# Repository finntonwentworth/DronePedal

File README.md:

# Drone Pedal/ Synth 

Repository for Drone pedal I have been working on and designing 

LFO Design from Skull and Circuits

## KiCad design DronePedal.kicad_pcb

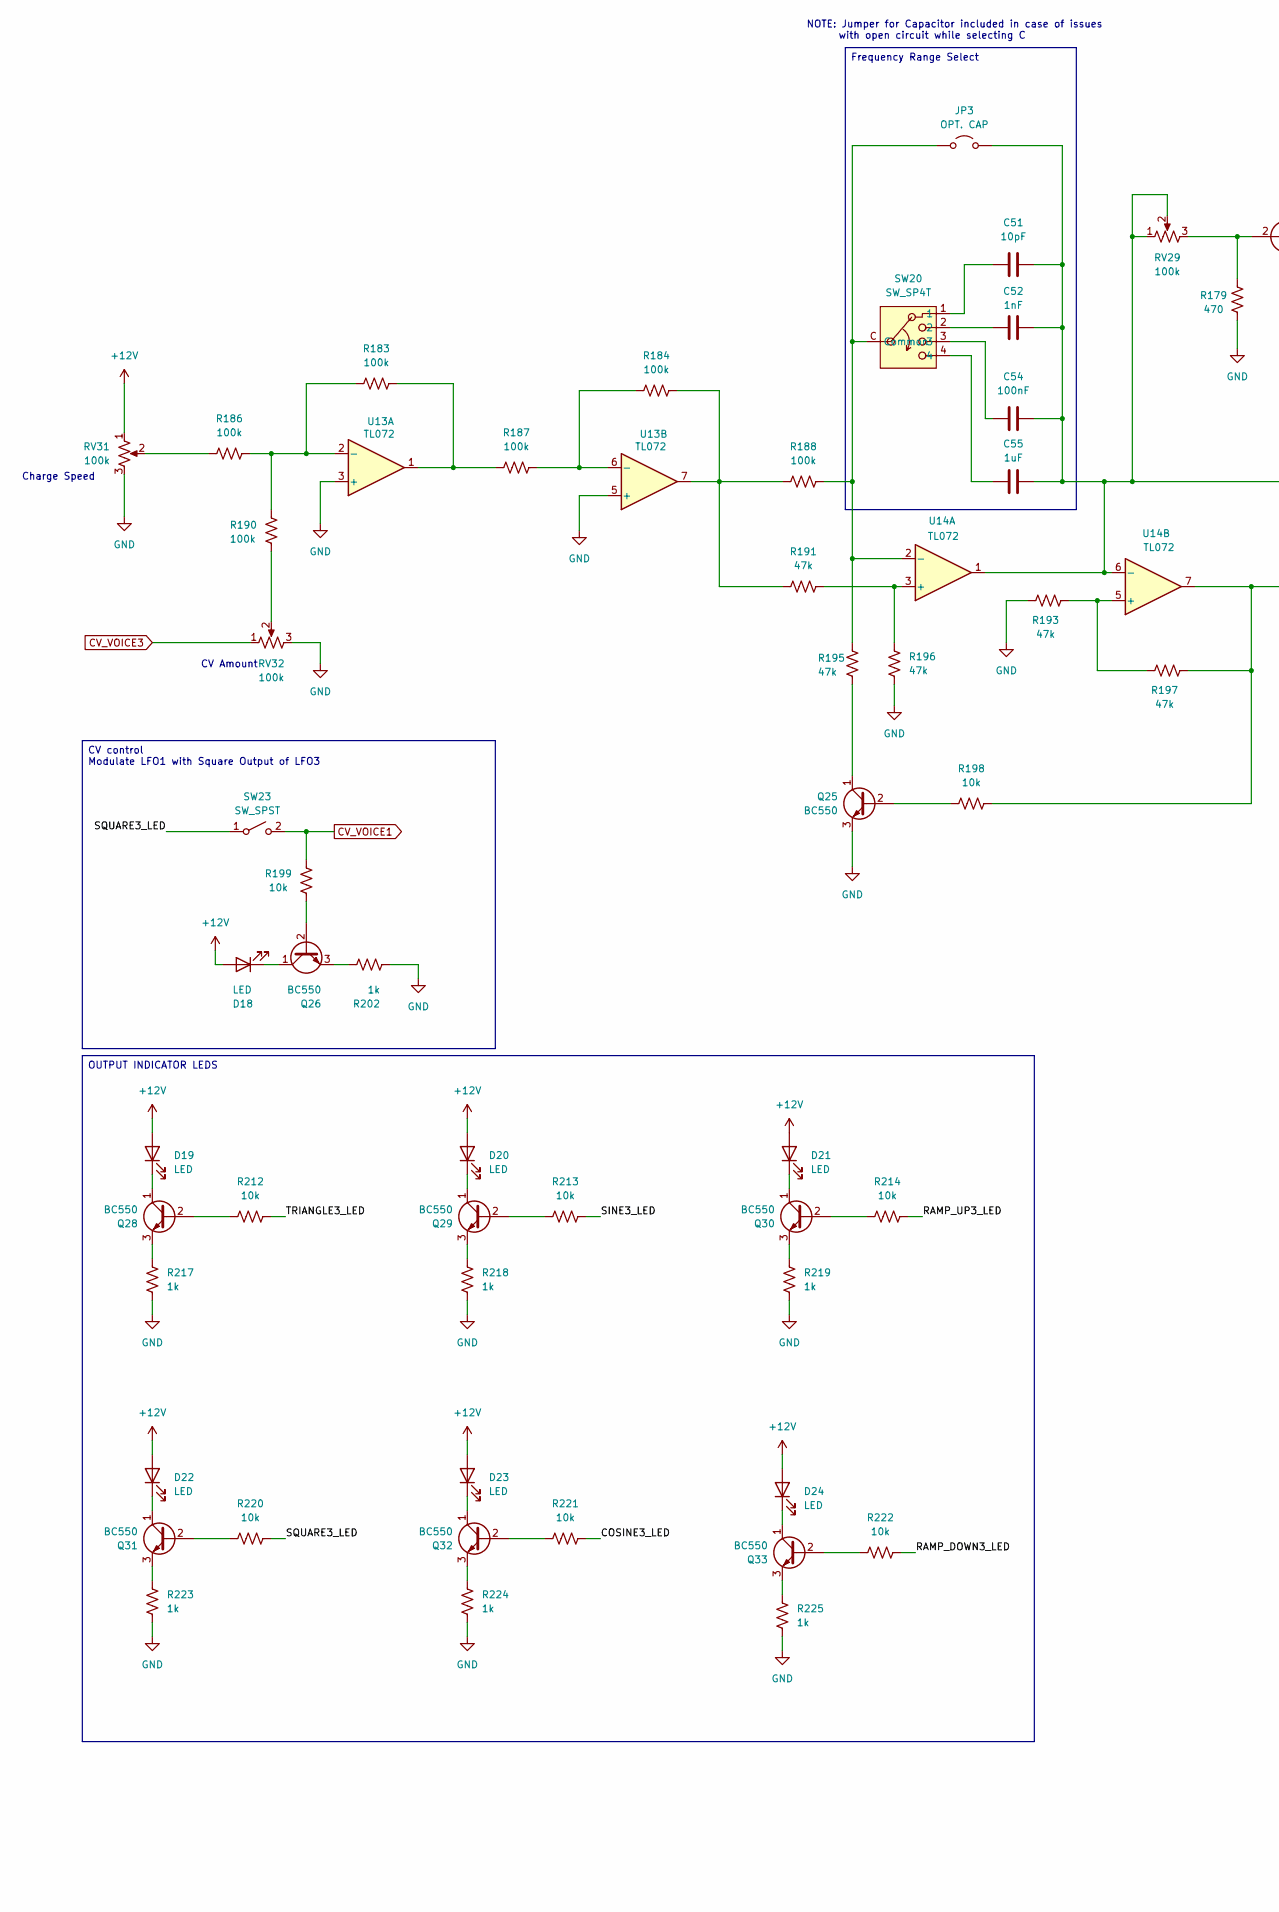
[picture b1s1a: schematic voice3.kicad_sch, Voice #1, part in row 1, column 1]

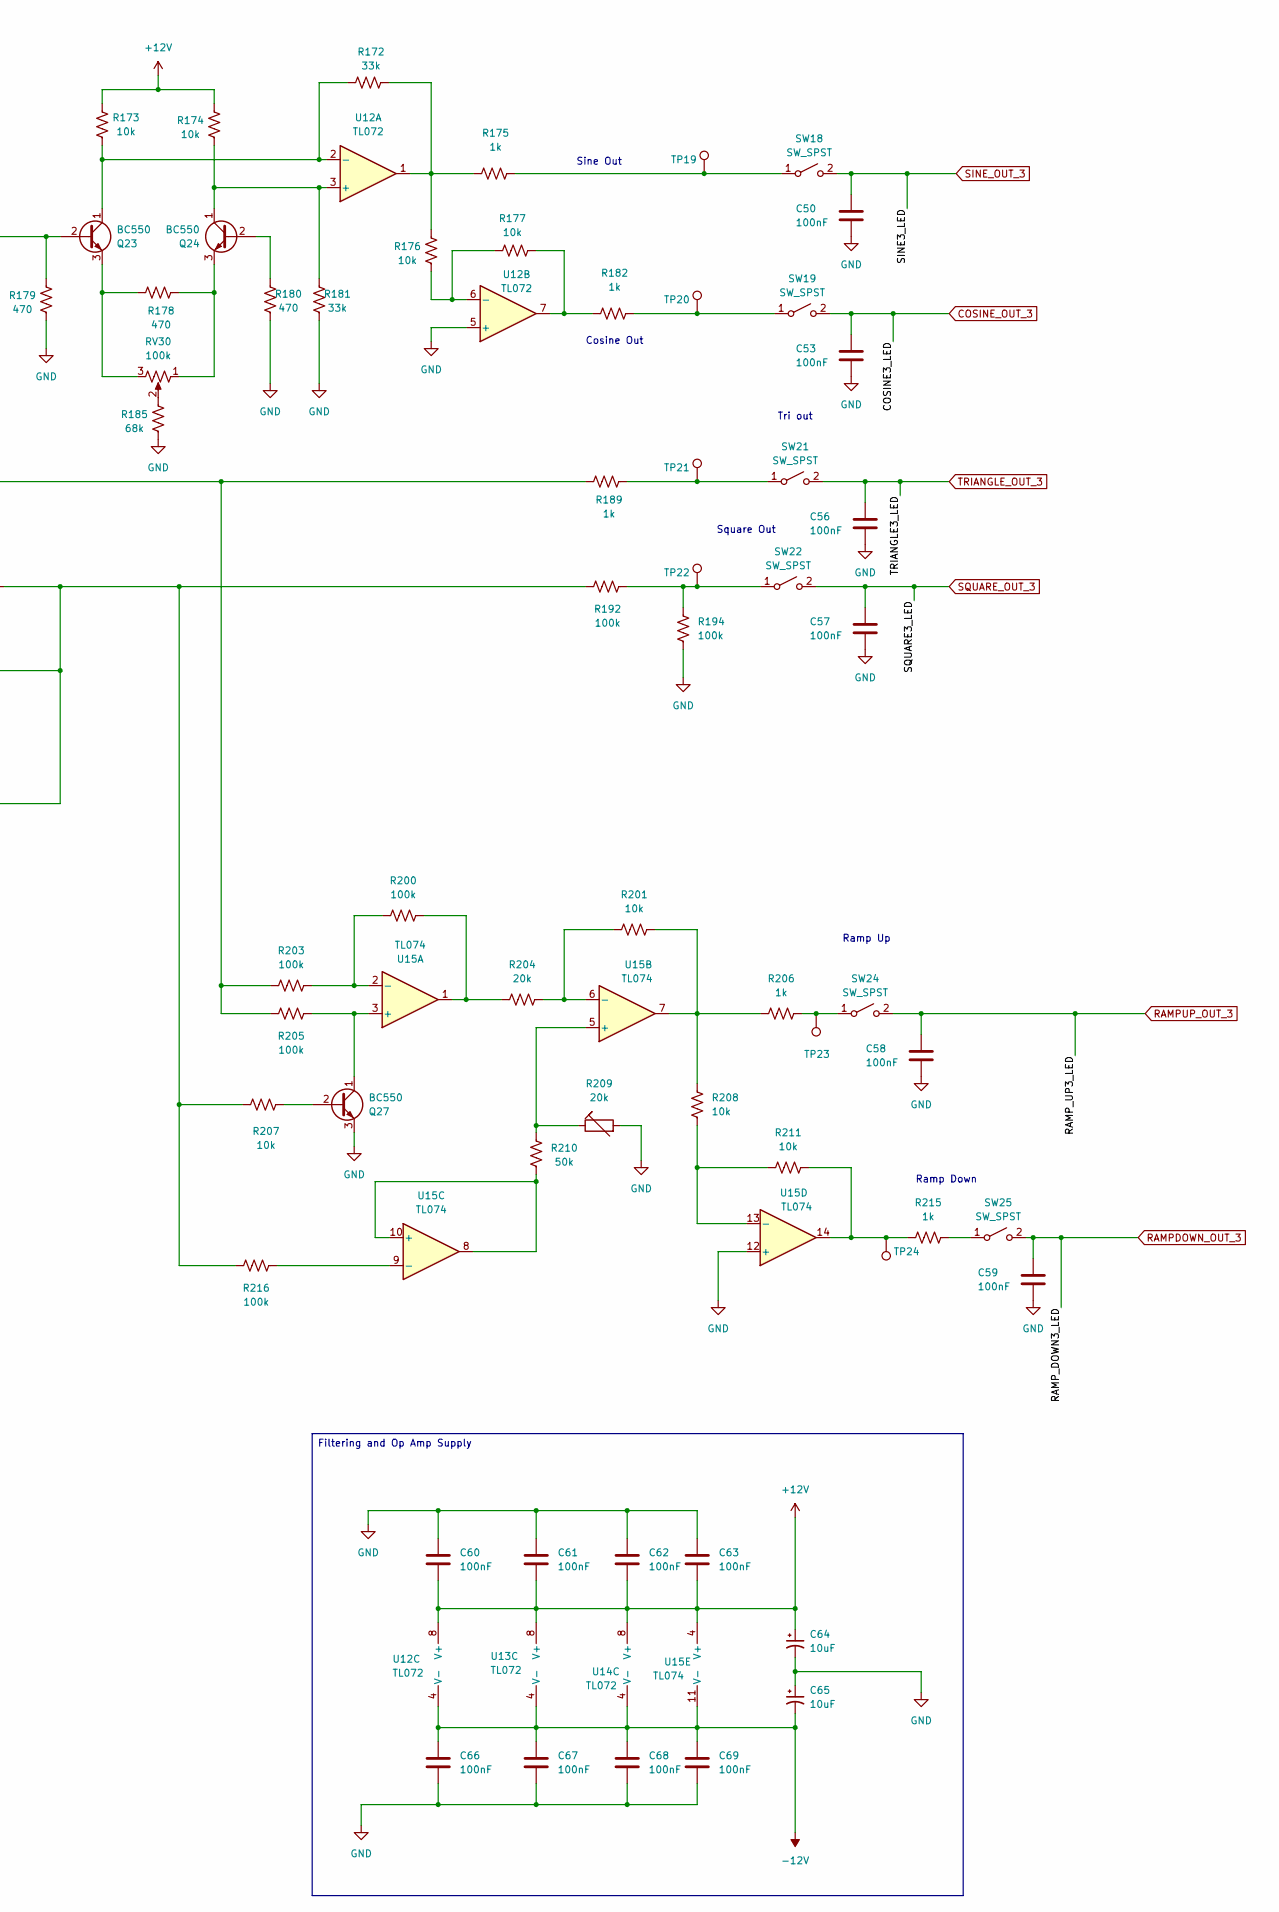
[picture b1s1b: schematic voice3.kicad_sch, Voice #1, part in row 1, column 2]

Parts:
C50, C53, C54, C56, C57, C58, C59, C60, C61, C62, C63, C66, C67, C68, C69: 100nF; C_Disc_D6.0mm_W2.5mm_P5.00mm
C51: 10pF; C_Disc_D4.7mm_W2.5mm_P5.00mm
C52: 1nF; C_Disc_D6.0mm_W2.5mm_P5.00mm
C55: 1uF; C_Disc_D5.0mm_W2.5mm_P2.50mm
C64, C65: 10uF; C_Disc_D6.0mm_W2.5mm_P5.00mm
D18, D19, D20, D21, D22, D23, D24: LED; LED_D1.8mm_W3.3mm_H2.4mm
JP3: OPT. CAP; C_Disc_D5.0mm_W2.5mm_P2.50mm
Q23, Q24, Q25, Q26, Q27, Q28, Q29, Q30, Q31, Q32, Q33: BC550; TO-92_Inline
R172, R181: 33k; R_Axial_DIN0204_L3.6mm_D1.6mm_P5.08mm_Horizontal
R173, R174, R176, R177, R198, R199, R201, R207, R208, R211, R212, R213, R214, R220, R221, R222: 10k; R_Axial_DIN0204_L3.6mm_D1.6mm_P5.08mm_Horizontal
R175, R182, R189, R202, R206, R215, R217, R218, R219, R223, R224, R225: 1k; R_Axial_DIN0204_L3.6mm_D1.6mm_P5.08mm_Horizontal
R178, R179, R180: 470; R_Axial_DIN0204_L3.6mm_D1.6mm_P5.08mm_Horizontal
R183, R184, R186, R187, R188, R190, R192, R194, R200, R203, R205, R216: 100k; R_Axial_DIN0207_L6.3mm_D2.5mm_P10.16mm_Horizontal
R185: 68k; R_Axial_DIN0204_L3.6mm_D1.6mm_P5.08mm_Horizontal
R191, R193, R195, R196, R197: 47k; R_Axial_DIN0204_L3.6mm_D1.6mm_P5.08mm_Horizontal
R204: 20k; R_Axial_DIN0204_L3.6mm_D1.6mm_P5.08mm_Horizontal
R209: 20k; PinHeader_1x03_P2.54mm_Vertical
R210: 50k; R_Axial_DIN0207_L6.3mm_D2.5mm_P7.62mm_Horizontal
RV29, RV30, RV31, RV32: 100k; PinHeader_1x03_P2.54mm_Vertical
SW18, SW19, SW21, SW22, SW23, SW24, SW25: SW_SPST; PinHeader_1x02_P2.54mm_Vertical
SW20: SW_SP4T; PinHeader_1x05_P2.54mm_Vertical
TP19, TP20, TP21, TP22, TP23, TP24: TestPoint_Pad_D1.0mm
U12, U13, U14: TL072; DIP-8_W7.62mm
U15: TL074; DIP-14_W7.62mm

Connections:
+12V: C60.2, C61.2, C62.2, C63.2, C64.1, D18.2 (A), D19.2 (A), D20.2 (A), D21.2 (A), D22.2 (A), D23.2 (A), D24.2 (A), R173.1, R174.1, RV31.1, U12.8 (V+), U13.8 (V+), U14.8 (V+), U15.4 (V+); also elsewhere on the board
-12V: C65.2, C66.1, C67.1, C68.1, C69.1, U12.4 (V-), U13.4 (V-), U14.4 (V-), U15.11 (V-); also elsewhere on the board
COSINE_OUT_3: C53.1, R221.2, SW19.2 (B); also elsewhere on the board
CV_VOICE1: R199.2, SW23.2 (B); also elsewhere on the board
CV_VOICE3: RV32.1; also elsewhere on the board
GND: C50.2, C53.2, C56.2, C57.2, C58.2, C59.2, C60.1, C61.1, C62.1, C63.1, C64.2, C65.1, C66.2, C67.2, C68.2, C69.2, Q25.3 (E), Q27.3 (E), R179.2, R180.1, R181.1, R185.2, R193.2, R194.1, R196.1, R202.1, R209.2, R217.1, R218.1, R219.1, R223.1, R224.1, R225.1, RV31.3, RV32.3, U12.5 (+), U13.3 (+), U13.5 (+), U15.12 (+); also elsewhere on the board
unnamed: C51.1, SW20.1
unnamed: C52.2, SW20.2
unnamed: C54.2, SW20.3
unnamed: C55.2, SW20.4
unnamed: D18.1 (K), Q26.1 (C)
unnamed: D19.1 (K), Q28.1 (C)
unnamed: D20.1 (K), Q29.1 (C)
unnamed: D21.1 (K), Q30.1 (C)
unnamed: D22.1 (K), Q31.1 (C)
unnamed: D23.1 (K), Q32.1 (C)
unnamed: D24.1 (K), Q33.1 (C)
unnamed: JP3.1 (A), R188.2, R195.2, SW20.C (Common), U14.2 (-)
unnamed: C51.2, C52.1, C54.1, C55.1, JP3.2 (B), R189.2, R203.1, R205.1, RV29.1, RV29.2, U14.1, U14.6 (-)
unnamed: Q23.2 (B), R179.1, RV29.3
unnamed: Q23.1 (C), R172.2, R173.2, U12.2 (-)
unnamed: Q23.3 (E), R178.1, RV30.3
unnamed: Q24.2 (B), R180.2
unnamed: Q24.1 (C), R174.2, R181.2, U12.3 (+)
unnamed: Q24.3 (E), R178.2, RV30.1
unnamed: Q25.2 (B), R198.1
unnamed: Q25.1 (C), R195.1
unnamed: Q26.2 (B), R199.1
unnamed: Q26.3 (E), R202.2
unnamed: Q27.2 (B), R207.2
unnamed: Q27.1 (C), R205.2, U15.3 (+)
unnamed: Q28.2 (B), R212.1
unnamed: Q28.3 (E), R217.2
unnamed: Q29.2 (B), R213.1
unnamed: Q29.3 (E), R218.2
unnamed: Q30.2 (B), R214.1
unnamed: Q30.3 (E), R219.2
unnamed: Q31.2 (B), R220.1
unnamed: Q31.3 (E), R223.2
unnamed: Q32.2 (B), R221.1
unnamed: Q32.3 (E), R224.2
unnamed: Q33.2 (B), R222.1
unnamed: Q33.3 (E), R225.2
unnamed: R172.1, R175.2, R176.1, U12.1
unnamed: R177.1, R182.2, U12.7
unnamed: R183.2, R187.1, U13.1
unnamed: R184.2, R188.1, R191.1, U13.7
unnamed: R185.1, RV30.2
unnamed: R186.1, RV31.2
unnamed: R190.1, RV32.2
unnamed: R192.1, R197.1, R198.2, R207.1, R216.1, U14.7
unnamed: R200.2, R204.1, U15.1
unnamed: R201.2, R206.1, R208.2, U15.7
unnamed: R211.1, R215.2, TP24.1, U15.14
unnamed: R175.1, SW18.1 (A), TP19.1
unnamed: R182.1, SW19.1 (A), TP20.1
unnamed: R189.1, SW21.1 (A), TP21.1
unnamed: R192.2, R194.2, SW22.1 (A), TP22.1
unnamed: R206.2, SW24.1 (A), TP23.1
unnamed: R215.1, SW25.1 (A)
unnamed: R176.2, R177.2, U12.6 (-)
unnamed: R183.1, R186.2, R190.2, U13.2 (-)
unnamed: R184.1, R187.2, U13.6 (-)
unnamed: R191.2, R196.2, U14.3 (+)
unnamed: R193.1, R197.2, U14.5 (+)
unnamed: R200.1, R203.2, U15.2 (-)
unnamed: R209.1, R210.2, U15.5 (+)
unnamed: R201.1, R204.2, U15.6 (-)
unnamed: R210.1, U15.8, U15.10 (+)
unnamed: R216.2, U15.9 (-)
unnamed: R208.1, R211.2, U15.13 (-)
RAMPDOWN_OUT_3: C59.1, R222.2, SW25.2 (B); also elsewhere on the board
RAMPUP_OUT_3: C58.1, R214.2, SW24.2 (B); also elsewhere on the board
SINE_OUT_3: C50.1, R213.2, SW18.2 (B); also elsewhere on the board
SQUARE_OUT_3: C57.1, R220.2, SW22.2 (B), SW23.1 (A); also elsewhere on the board
TRIANGLE_OUT_3: C56.1, R212.2, SW21.2 (B); also elsewhere on the board

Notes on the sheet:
NOTE: Jumper for Capacitor included in case of issues with open circuit while selecting C
Charge Speed
CV Amount
Square Out
Sine Out
Tri out
Cosine Out
Ramp Up
Ramp Down
Frequency Range Select
CV control Modulate LFO1 with Square Output of LFO3
OUTPUT INDICATOR LEDS
Filtering and Op Amp Supply

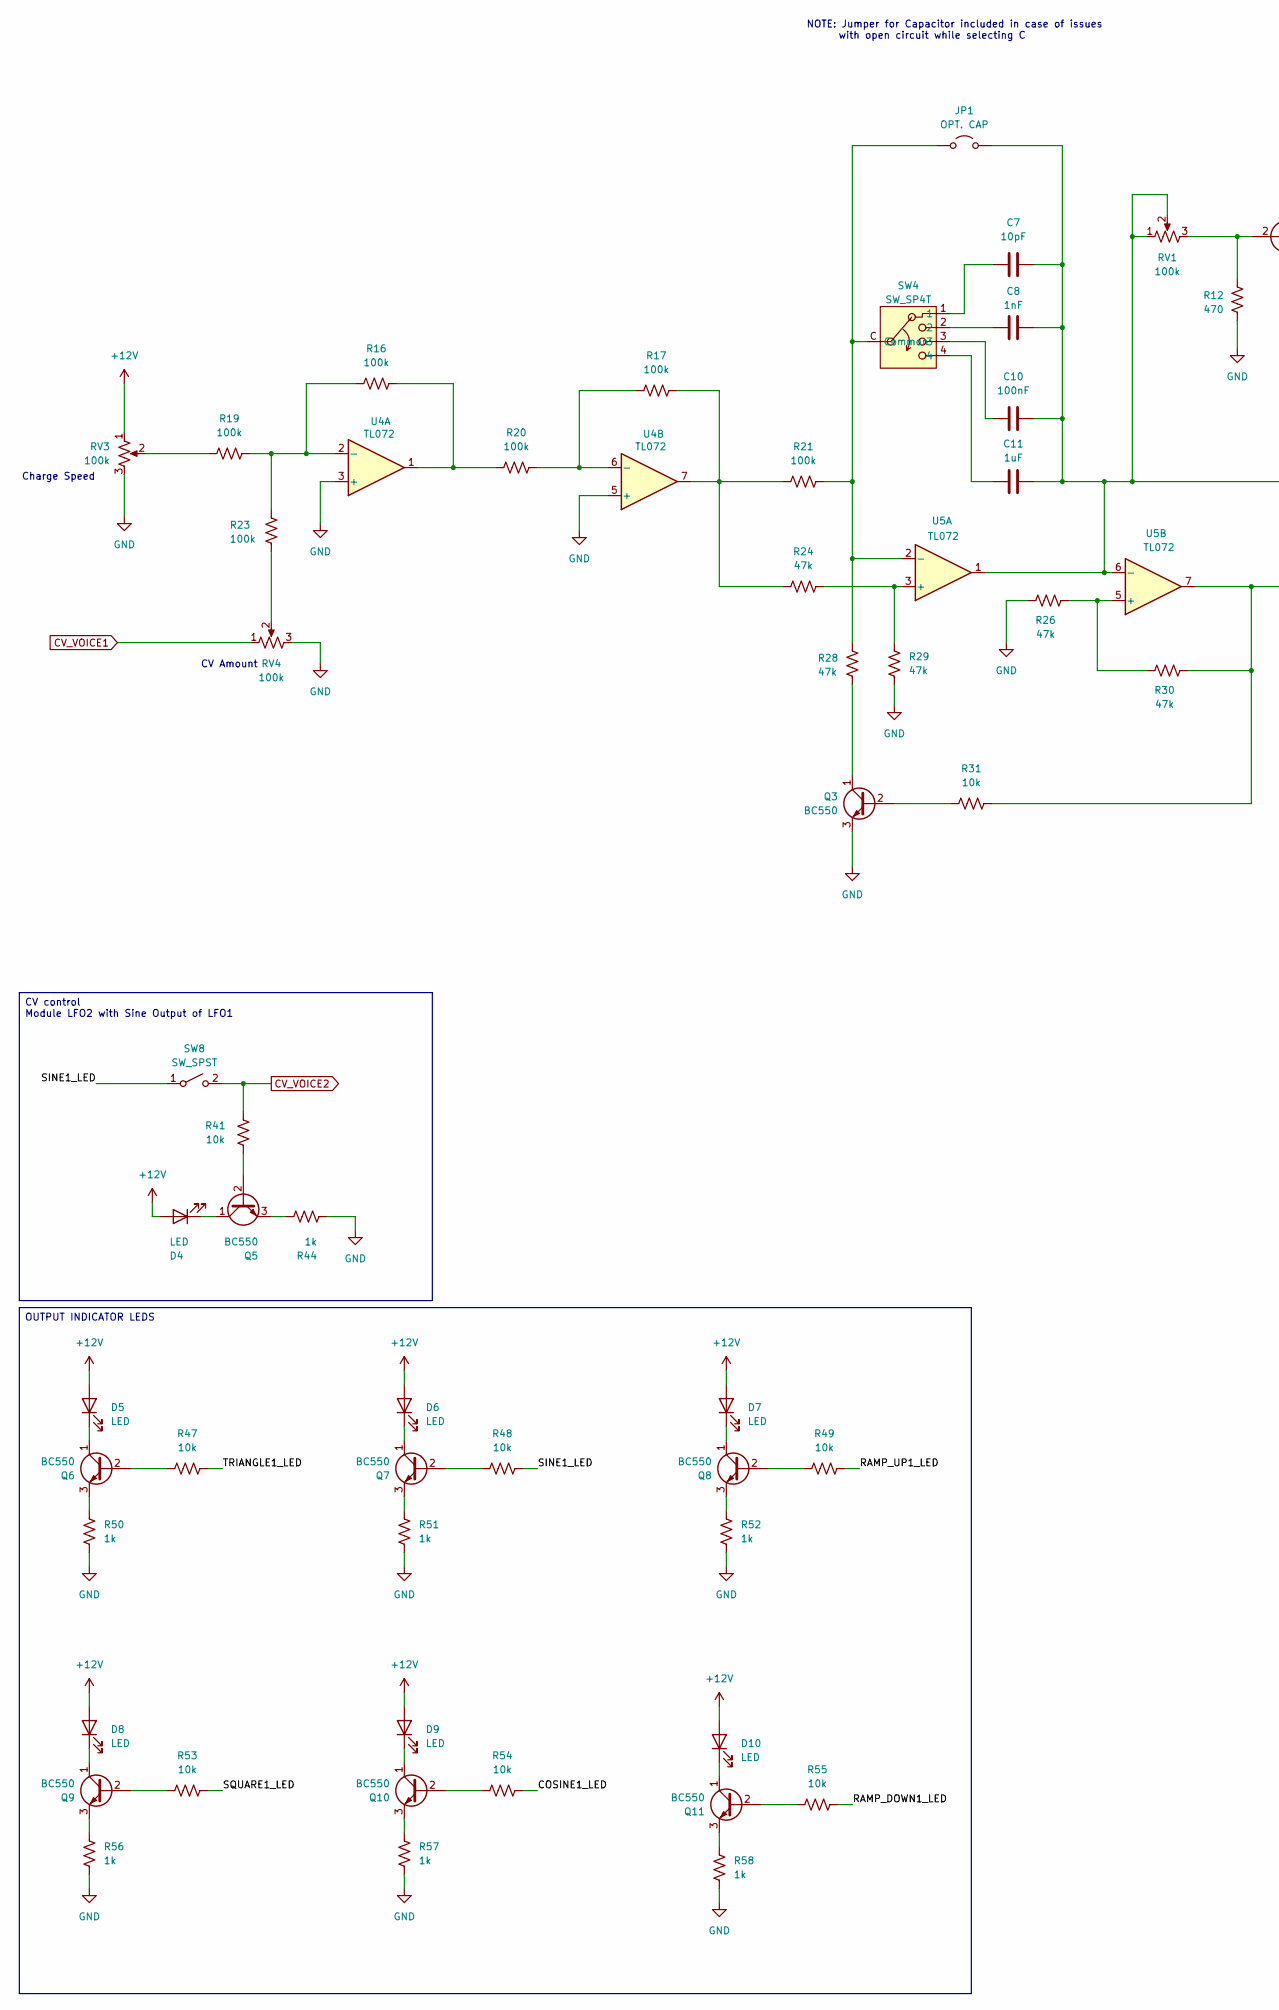
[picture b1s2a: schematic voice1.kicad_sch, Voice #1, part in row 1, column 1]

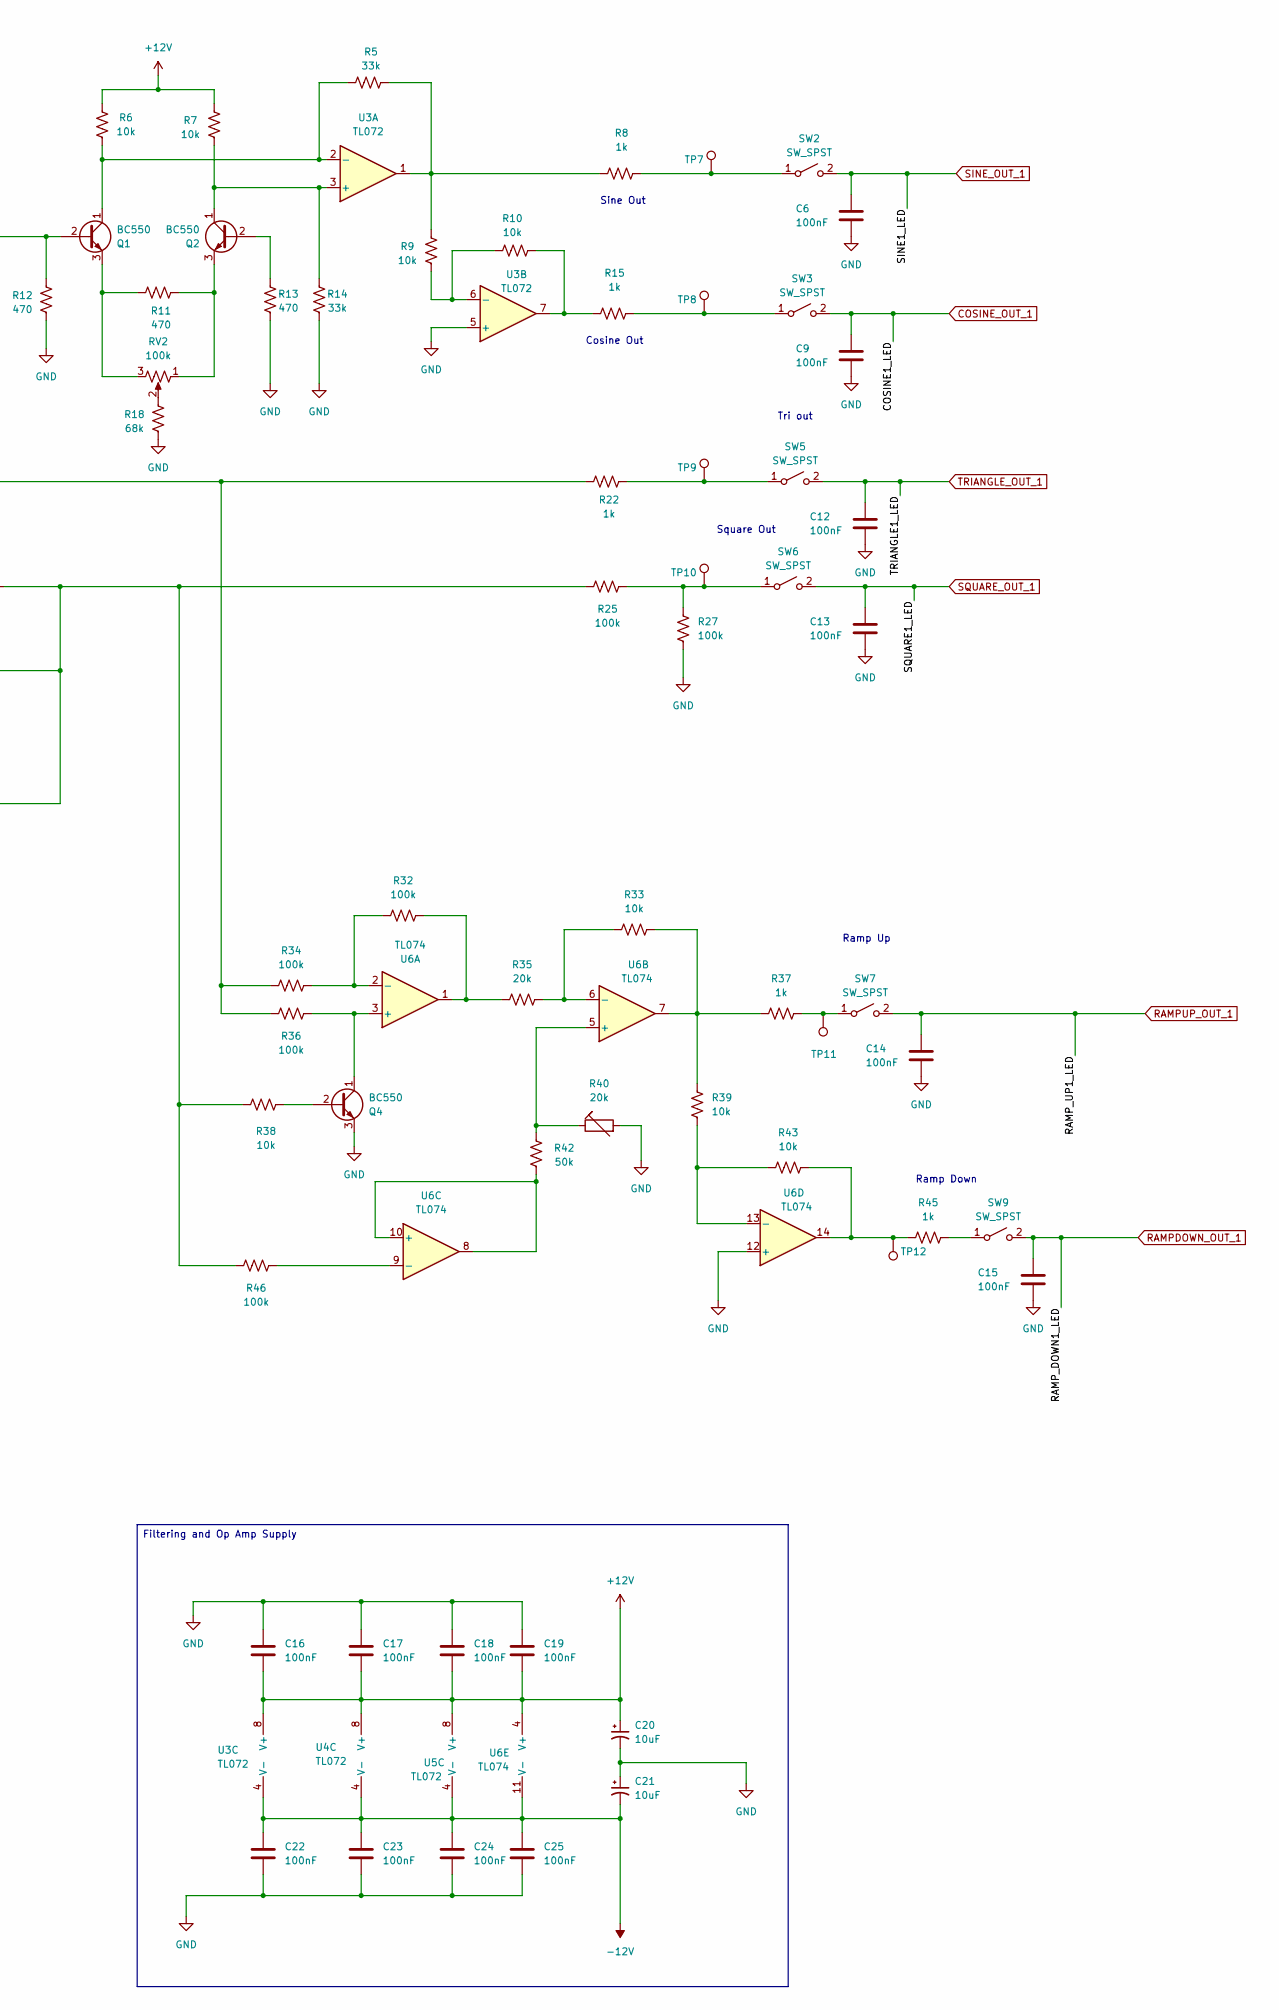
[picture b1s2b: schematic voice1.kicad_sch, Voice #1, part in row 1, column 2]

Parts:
C6, C9, C10, C12, C13, C14, C15, C16, C17, C18, C19, C22, C23, C24, C25: 100nF; C_Disc_D6.0mm_W2.5mm_P5.00mm
C7: 10pF; C_Disc_D4.7mm_W2.5mm_P5.00mm
C8: 1nF; C_Disc_D6.0mm_W2.5mm_P5.00mm
C11: 1uF; C_Disc_D5.0mm_W2.5mm_P2.50mm
C20, C21: 10uF; C_Disc_D6.0mm_W2.5mm_P5.00mm
D4, D5, D6, D7, D8, D9, D10: LED; LED_D1.8mm_W3.3mm_H2.4mm
JP1: OPT. CAP; C_Disc_D5.0mm_W2.5mm_P2.50mm
Q1, Q2, Q3, Q4, Q5, Q6, Q7, Q8, Q9, Q10, Q11: BC550; TO-92_Inline
R5, R14: 33k; R_Axial_DIN0204_L3.6mm_D1.6mm_P5.08mm_Horizontal
R6, R7, R9, R10, R31, R33, R38, R39, R41, R43, R47, R48, R49, R53, R54, R55: 10k; R_Axial_DIN0204_L3.6mm_D1.6mm_P5.08mm_Horizontal
R8, R15, R22, R37, R44, R45, R50, R51, R52, R56, R57, R58: 1k; R_Axial_DIN0204_L3.6mm_D1.6mm_P5.08mm_Horizontal
R11, R12, R13: 470; R_Axial_DIN0204_L3.6mm_D1.6mm_P5.08mm_Horizontal
R16, R17, R19, R20, R21, R23, R25, R27, R32, R34, R36, R46: 100k; R_Axial_DIN0207_L6.3mm_D2.5mm_P10.16mm_Horizontal
R18: 68k; R_Axial_DIN0204_L3.6mm_D1.6mm_P5.08mm_Horizontal
R24, R26, R28, R29, R30: 47k; R_Axial_DIN0204_L3.6mm_D1.6mm_P5.08mm_Horizontal
R35: 20k; R_Axial_DIN0204_L3.6mm_D1.6mm_P5.08mm_Horizontal
R40: 20k; PinHeader_1x03_P2.54mm_Vertical
R42: 50k; R_Axial_DIN0207_L6.3mm_D2.5mm_P7.62mm_Horizontal
RV1, RV2, RV3, RV4: 100k; PinHeader_1x03_P2.54mm_Vertical
SW2, SW3, SW5, SW6, SW7, SW8, SW9: SW_SPST; PinHeader_1x02_P2.54mm_Vertical
SW4: SW_SP4T; PinHeader_1x05_P2.54mm_Vertical
TP7, TP8, TP9, TP10, TP11, TP12: TestPoint_Pad_D1.0mm
U3, U4, U5: TL072; DIP-8_W7.62mm
U6: TL074; DIP-14_W7.62mm

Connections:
+12V: C16.2, C17.2, C18.2, C19.2, C20.1, D4.2 (A), D5.2 (A), D6.2 (A), D7.2 (A), D8.2 (A), D9.2 (A), D10.2 (A), R6.1, R7.1, RV3.1, U3.8 (V+), U4.8 (V+), U5.8 (V+), U6.4 (V+); also elsewhere on the board
-12V: C21.2, C22.1, C23.1, C24.1, C25.1, U3.4 (V-), U4.4 (V-), U5.4 (V-), U6.11 (V-); also elsewhere on the board
COSINE_OUT_1: C9.1, R54.2, SW3.2 (B); also elsewhere on the board
CV_VOICE1: RV4.1; also elsewhere on the board
CV_VOICE2: R41.2, SW8.2 (B); also elsewhere on the board
GND: C6.2, C9.2, C12.2, C13.2, C14.2, C15.2, C16.1, C17.1, C18.1, C19.1, C20.2, C21.1, C22.2, C23.2, C24.2, C25.2, Q3.3 (E), Q4.3 (E), R12.2, R13.1, R14.1, R18.2, R26.2, R27.1, R29.1, R40.2, R44.1, R50.1, R51.1, R52.1, R56.1, R57.1, R58.1, RV3.3, RV4.3, U3.5 (+), U4.3 (+), U4.5 (+), U6.12 (+); also elsewhere on the board
unnamed: C7.1, SW4.1
unnamed: C8.2, SW4.2
unnamed: C10.2, SW4.3
unnamed: C11.2, SW4.4
unnamed: D4.1 (K), Q5.1 (C)
unnamed: D5.1 (K), Q6.1 (C)
unnamed: D6.1 (K), Q7.1 (C)
unnamed: D7.1 (K), Q8.1 (C)
unnamed: D8.1 (K), Q9.1 (C)
unnamed: D9.1 (K), Q10.1 (C)
unnamed: D10.1 (K), Q11.1 (C)
unnamed: JP1.1 (A), R21.2, R28.2, SW4.C (Common), U5.2 (-)
unnamed: C7.2, C8.1, C10.1, C11.1, JP1.2 (B), R22.2, R34.1, R36.1, RV1.1, RV1.2, U5.1, U5.6 (-)
unnamed: Q1.2 (B), R12.1, RV1.3
unnamed: Q1.1 (C), R5.2, R6.2, U3.2 (-)
unnamed: Q1.3 (E), R11.1, RV2.3
unnamed: Q2.2 (B), R13.2
unnamed: Q2.1 (C), R7.2, R14.2, U3.3 (+)
unnamed: Q2.3 (E), R11.2, RV2.1
unnamed: Q3.2 (B), R31.1
unnamed: Q3.1 (C), R28.1
unnamed: Q4.2 (B), R38.2
unnamed: Q4.1 (C), R36.2, U6.3 (+)
unnamed: Q5.2 (B), R41.1
unnamed: Q5.3 (E), R44.2
unnamed: Q6.2 (B), R47.1
unnamed: Q6.3 (E), R50.2
unnamed: Q7.2 (B), R48.1
unnamed: Q7.3 (E), R51.2
unnamed: Q8.2 (B), R49.1
unnamed: Q8.3 (E), R52.2
unnamed: Q9.2 (B), R53.1
unnamed: Q9.3 (E), R56.2
unnamed: Q10.2 (B), R54.1
unnamed: Q10.3 (E), R57.2
unnamed: Q11.2 (B), R55.1
unnamed: Q11.3 (E), R58.2
unnamed: R5.1, R8.2, R9.1, U3.1
unnamed: R10.1, R15.2, U3.7
unnamed: R16.2, R20.1, U4.1
unnamed: R17.2, R21.1, R24.1, U4.7
unnamed: R18.1, RV2.2
unnamed: R19.1, RV3.2
unnamed: R23.1, RV4.2
unnamed: R25.1, R30.1, R31.2, R38.1, R46.1, U5.7
unnamed: R32.2, R35.1, U6.1
unnamed: R33.2, R37.1, R39.2, U6.7
unnamed: R43.1, R45.2, TP12.1, U6.14
unnamed: R8.1, SW2.1 (A), TP7.1
unnamed: R15.1, SW3.1 (A), TP8.1
unnamed: R22.1, SW5.1 (A), TP9.1
unnamed: R25.2, R27.2, SW6.1 (A), TP10.1
unnamed: R37.2, SW7.1 (A), TP11.1
unnamed: R45.1, SW9.1 (A)
unnamed: R9.2, R10.2, U3.6 (-)
unnamed: R16.1, R19.2, R23.2, U4.2 (-)
unnamed: R17.1, R20.2, U4.6 (-)
unnamed: R24.2, R29.2, U5.3 (+)
unnamed: R26.1, R30.2, U5.5 (+)
unnamed: R32.1, R34.2, U6.2 (-)
unnamed: R40.1, R42.2, U6.5 (+)
unnamed: R33.1, R35.2, U6.6 (-)
unnamed: R42.1, U6.8, U6.10 (+)
unnamed: R46.2, U6.9 (-)
unnamed: R39.1, R43.2, U6.13 (-)
RAMPDOWN_OUT_1: C15.1, R55.2, SW9.2 (B); also elsewhere on the board
RAMPUP_OUT_1: C14.1, R49.2, SW7.2 (B); also elsewhere on the board
SINE_OUT_1: C6.1, R48.2, SW2.2 (B), SW8.1 (A); also elsewhere on the board
SQUARE_OUT_1: C13.1, R53.2, SW6.2 (B); also elsewhere on the board
TRIANGLE_OUT_1: C12.1, R47.2, SW5.2 (B); also elsewhere on the board

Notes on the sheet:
Square Out
Ramp Up
Tri out
CV Amount
NOTE: Jumper for Capacitor included in case of issues with open circuit while selecting C
Sine Out
Ramp Down
Cosine Out
Charge Speed
CV control Module LFO2 with Sine Output of LFO1
Filtering and Op Amp Supply
OUTPUT INDICATOR LEDS

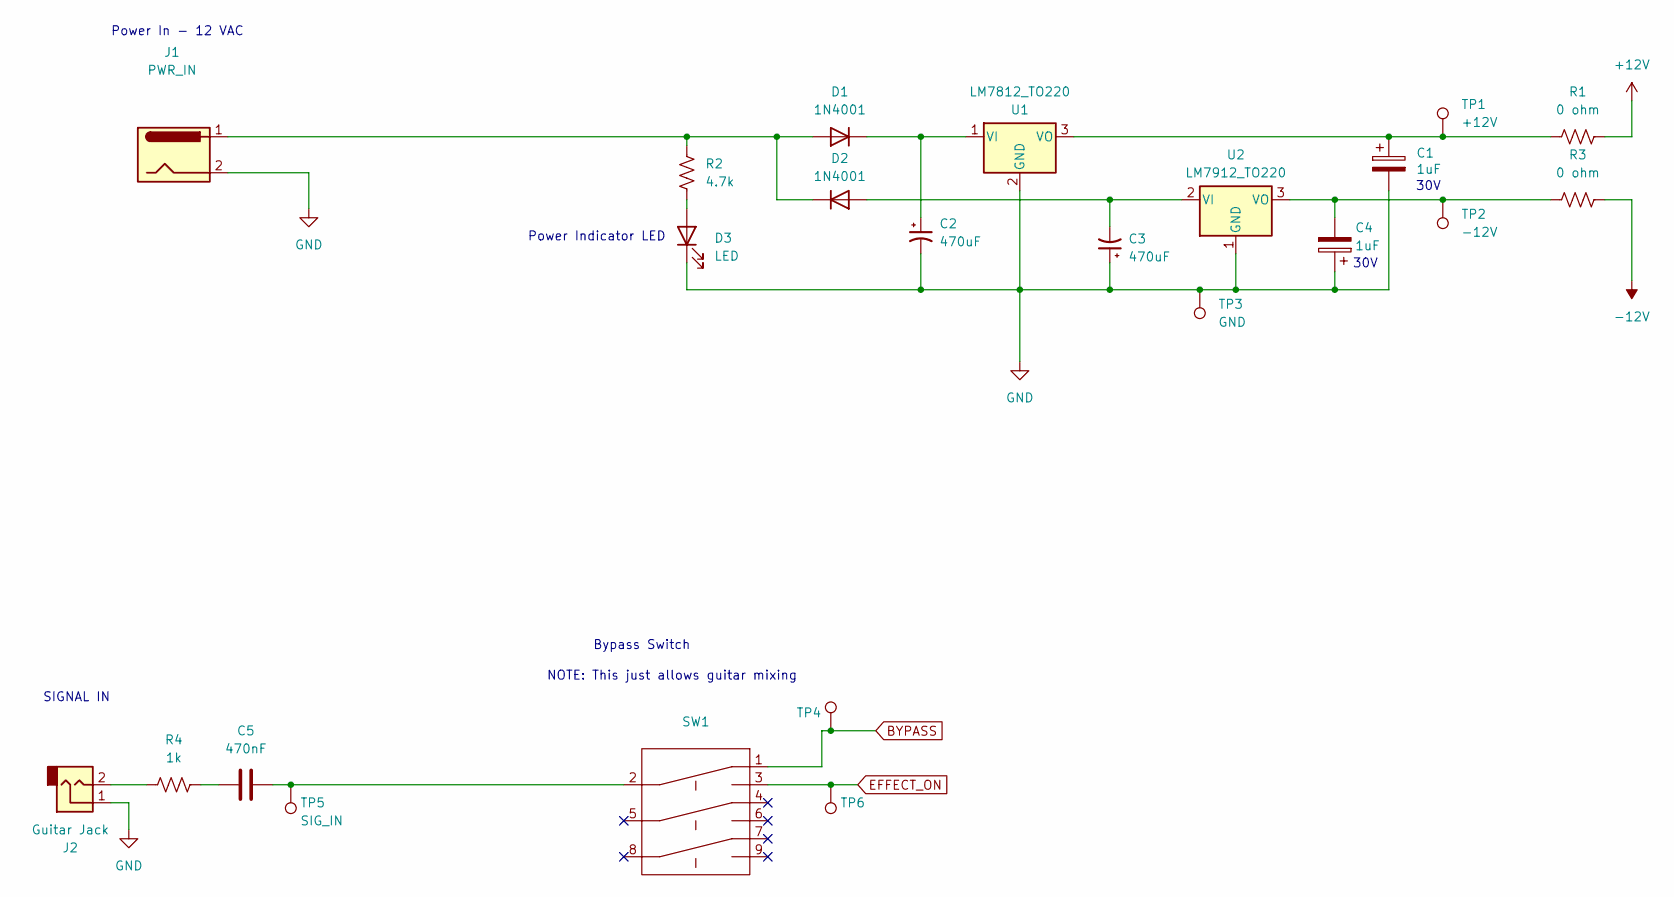
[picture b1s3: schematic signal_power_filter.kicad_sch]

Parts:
C1, C4: 1uF; CP_Radial_D5.0mm_P2.00mm
C2, C3: 470uF; CP_Radial_D10.0mm_P5.00mm
C5: 470nF; C_Disc_D5.0mm_W2.5mm_P2.50mm
D1, D2: 1N4001; D_DO-41_SOD81_P7.62mm_Horizontal
D3: LED; LED_D1.8mm_W3.3mm_H2.4mm
J1: PWR_IN; PinHeader_1x02_P2.54mm_Vertical
J2: Guitar Jack; PinHeader_1x02_P2.54mm_Vertical
R1, R3: 0 ohm; PinHeader_1x02_P1.00mm_Vertical
R2: 4.7k; R_Axial_DIN0204_L3.6mm_D1.6mm_P5.08mm_Horizontal
R4: 1k; R_Axial_DIN0204_L3.6mm_D1.6mm_P5.08mm_Horizontal
SW1: PinSocket_1x09_P2.54mm_Vertical
TP1: +12V; TestPoint_Pad_D1.0mm
TP2: -12V; TestPoint_Pad_D1.0mm
TP3: GND; TestPoint_Pad_D1.0mm
TP4, TP6: TestPoint_Pad_D1.0mm
TP5: SIG_IN; TestPoint_Pad_D1.0mm
U1: LM7812_TO220; TO-220-3_Horizontal_TabDown
U2: LM7912_TO220; TO-220-3_Horizontal_TabDown

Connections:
+12V: R1.2; also elsewhere on the board
-12V: R3.2; also elsewhere on the board
BYPASS: SW1.1, TP4.1; also elsewhere on the board
EFFECT_ON: SW1.3, TP6.1; also elsewhere on the board
GND: C1.2, C2.2, C3.1, C4.1, D3.1 (K), J1.2, J2.1, TP3.1, U1.2 (GND), U2.1 (GND); also elsewhere on the board
unnamed: C5.1, R4.2
unnamed: C5.2, SW1.2, TP5.1
unnamed: D1.2 (A), D2.1 (K), J1.1, R2.1
unnamed: C2.1, D1.1 (K), U1.1 (VI)
unnamed: C3.2, D2.2 (A), U2.2 (VI)
unnamed: D3.2 (A), R2.2
unnamed: J2.2, R4.1
unnamed: C1.1, R1.1, TP1.1, U1.3 (VO)
unnamed: C4.2, R3.1, TP2.1, U2.3 (VO)

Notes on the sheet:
Bypass Switch
Power Indicator LED
Power In - 12 VAC
30V
NOTE: This just allows guitar mixing
SIGNAL IN
